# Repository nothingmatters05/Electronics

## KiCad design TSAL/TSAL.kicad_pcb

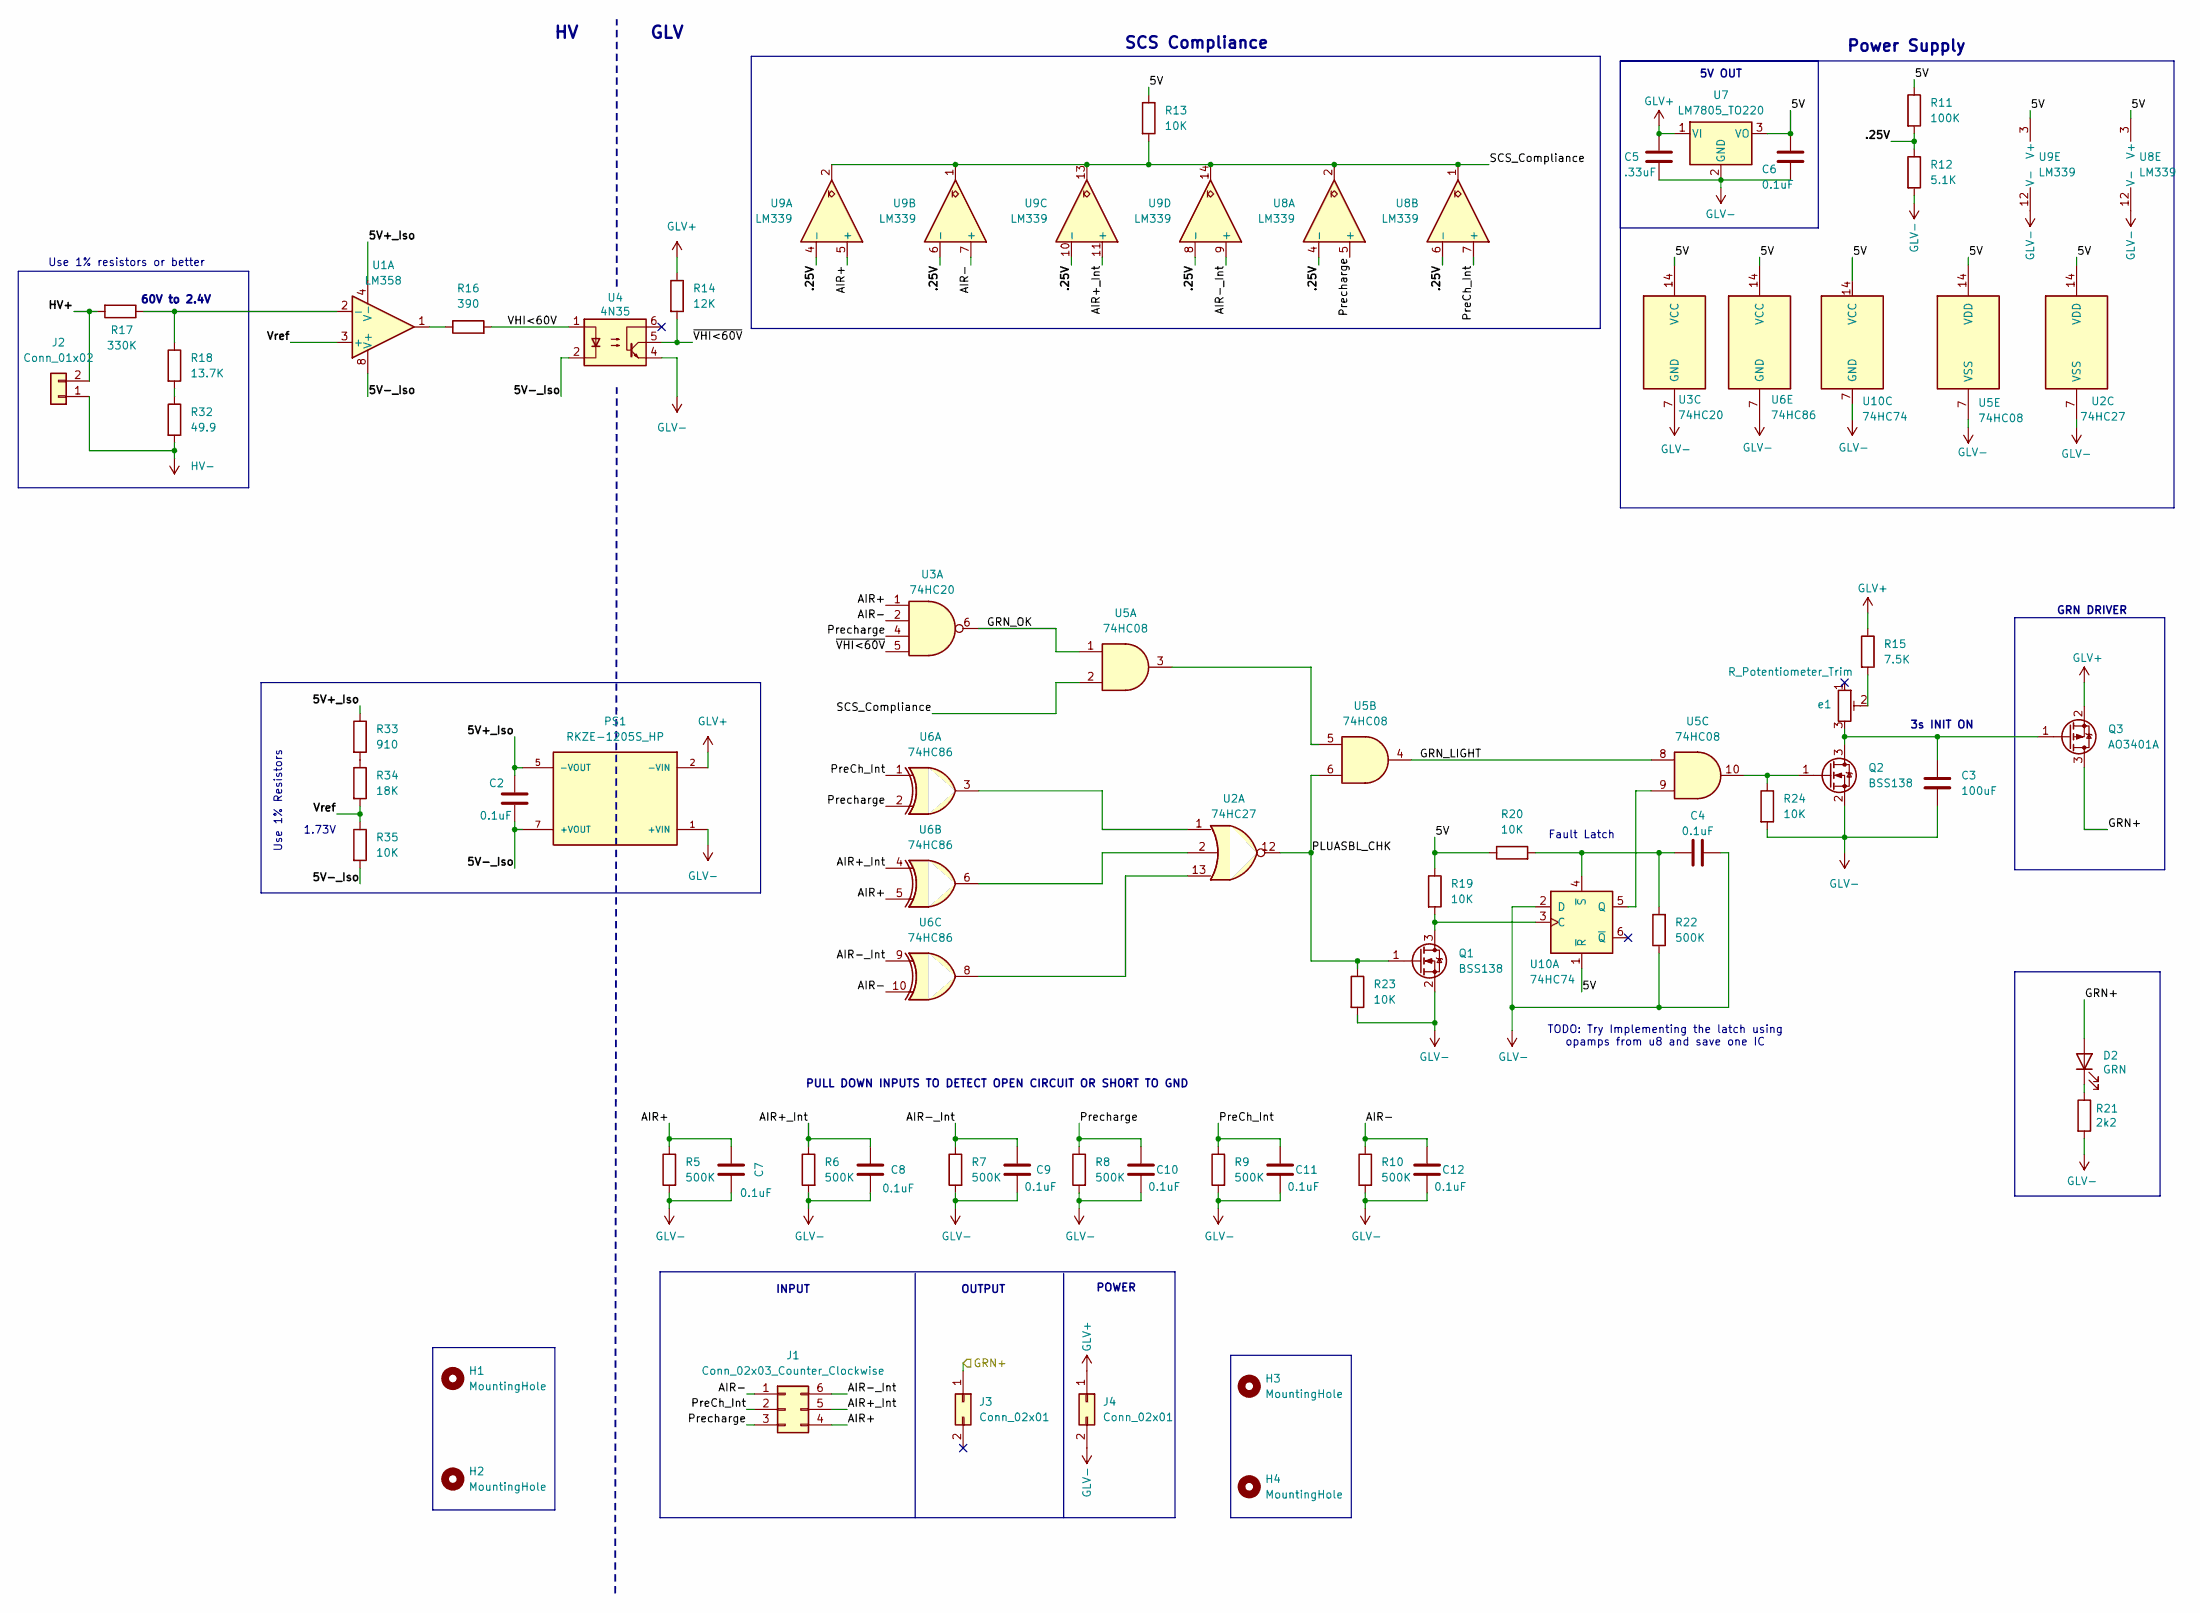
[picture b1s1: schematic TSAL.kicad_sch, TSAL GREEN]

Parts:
C2, C4, C6, C7, C8, C9, C10, C11, C12: 0.1uF; C_0603_1608Metric_Pad1.08x0.95mm_HandSolder
C3: 100uF; C_Elec_6.3x7.7
C5: .33uF; C_0603_1608Metric_Pad1.08x0.95mm_HandSolder
D2: GRN; LED_0805_2012Metric_Pad1.15x1.40mm_HandSolder
H1, H2, H3, H4: MountingHole; MountingHole_3.2mm_M3_DIN965
J1: Conn_02x03_Counter_Clockwise; Molex_Micro-Fit_3.0_43045-0612_2x03_P3.00mm_Vertical
J2: Conn_01x02; Molex_Mini-Fit_Jr_5566-02A_2x01_P4.20mm_Vertical
J3, J4: Conn_02x01; Molex_Micro-Fit_3.0_43045-0212_2x01_P3.00mm_Vertical
PS1: RKZE-1205S_HP; CONV_RKZE-1205S_HP
Q1, Q2: BSS138; SOT-23
Q3: AO3401A; SOT-23
R5, R6, R7, R8, R9, R10, R22: 500K; R_0603_1608Metric_Pad0.98x0.95mm_HandSolder
R11: 100K; R_0603_1608Metric_Pad0.98x0.95mm_HandSolder
R12: 5.1K; R_0603_1608Metric_Pad0.98x0.95mm_HandSolder
R13, R19, R20, R23, R24, R35: 10K; R_0603_1608Metric_Pad0.98x0.95mm_HandSolder
R14: 12K; R_0603_1608Metric_Pad0.98x0.95mm_HandSolder
R15: 7.5K; R_0603_1608Metric_Pad0.98x0.95mm_HandSolder
R16: 390; R_0603_1608Metric_Pad0.98x0.95mm_HandSolder
R17: 330K; R_1206_3216Metric_Pad1.30x1.75mm_HandSolder
R18: 13.7K; R_1206_3216Metric_Pad1.30x1.75mm_HandSolder
R21: 2k2; R_0603_1608Metric_Pad0.98x0.95mm_HandSolder
R32: 49.9; R_1206_3216Metric_Pad1.30x1.75mm_HandSolder
R33: 910; R_0603_1608Metric_Pad0.98x0.95mm_HandSolder
R34: 18K; R_0603_1608Metric_Pad0.98x0.95mm_HandSolder
U1: LM358; SOIC-8_3.9x4.9mm_P1.27mm
U2: 74HC27; SOIC-14_3.9x8.7mm_P1.27mm
U3: 74HC20; DIP-14_W7.62mm
U4: 4N35; DIP-6_W7.62mm
U5: 74HC08; DIP-14_W7.62mm
U6: 74HC86; DIP-14_W7.62mm
U7: LM7805_TO220; TO-220-3_Horizontal_TabDown
U8, U9: LM339; DIP-14_W7.62mm
U10: 74HC74; DIP-14_W7.62mm
e1: R_Potentiometer_Trim; Potentiometer_Bourns_3386F_Vertical

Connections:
/5V: C6.2, R11.1, R13.1, R19.1, R20.1, U2.14 (VDD), U3.14 (VCC), U5.14 (VDD), U6.14 (VCC), U7.3 (VO), U8.3 (V+), U9.3 (V+), U10.1 (~R), U10.14 (VCC)
/5V+_Iso: C2.1, PS1.5 (-VOUT), R33.1, U1.4 (V-)
/5V-_Iso: C2.2, PS1.7 (+VOUT), R35.2, U1.8 (V+), U4.2
/.25V: R11.2, R12.1, U8.4 (-), U8.6 (-), U9.4 (-), U9.6 (-), U9.8 (-), U9.10 (-)
/AIR+: C7.1, J1.4, R5.1, U3.1, U6.5, U9.5 (+)
/AIR+_Int: C8.1, J1.5, R6.1, U6.4, U9.11 (+)
/AIR-: C12.1, J1.1, R10.1, U3.2, U6.10, U9.7 (+)
/AIR-_Int: C9.1, J1.6, R7.1, U6.9, U9.9 (+)
/GRN+: D2.2 (A), J3.1, Q3.3 (D)
/GRN_LIGHT: U5.4, U5.8
/GRN_OK: U3.6, U5.1
/HV+: J2.2, R17.2
/PLUASBL_CHK: Q1.1 (G), U2.12, U5.6
/PreCh_Int: C11.1, J1.2, R9.1, U6.1, U8.7 (+)
/Precharge: C10.1, J1.3, R8.1, U3.4, U6.2, U8.5 (+)
/SCS_Compliance: R13.2, U5.2, U8.1, U8.2, U9.1, U9.2, U9.13, U9.14
/VHI<60V: R16.2, U4.1
/Vref: R34.2, R35.1, U1.3 (+)
/~VHI<60V: R14.2, U3.5, U4.5
GLV+: C5.1, J4.1, PS1.2 (-VIN), Q3.2 (S), R14.1, R15.1, U7.1 (VI)
GLV-: C3.2, C4.2, C5.2, C6.1, C7.2, C8.2, C9.2, C10.2, C11.2, C12.2, J4.2, PS1.1 (+VIN), Q1.2 (S), Q2.2 (S), R5.2, R6.2, R7.2, R8.2, R9.2, R10.2, R12.2, R21.2, R22.1, U2.7 (VSS), U3.7 (GND), U4.4, U5.7 (VSS), U6.7 (GND), U7.2 (GND), U8.12 (V-), U9.12 (V-), U10.2 (D), U10.7 (GND)
HV-: J2.1, R32.2
unnamed: D2.1 (K), R21.1
unnamed: Q1.3 (D), R19.2, U10.3 (C)
unnamed: C3.1, Q2.3 (D), Q3.1 (G), e1.3
unnamed: Q2.1 (G), U5.10
unnamed: R15.2, e1.2
unnamed: R16.1, U1.1
unnamed: R18.2, R32.1
unnamed: R33.2, R34.1
unnamed: R17.1, R18.1, U1.2 (-)
unnamed: U2.1, U6.3
unnamed: U2.2, U6.6
unnamed: U2.13, U6.8
unnamed: U5.3, U5.5
unnamed: U5.9, U10.5 (Q)
unnamed: C4.1, R20.2, R22.2, U10.4 (~S)

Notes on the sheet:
GLV
3s INIT ON
Power Supply
60V to 2.4V
GRN DRIVER
INPUT
TODO: Try Implementing the latch using opamps from u8 and save one IC
POWER
OUTPUT
PULL DOWN INPUTS TO DETECT OPEN CIRCUIT OR SHORT TO GND
Use 1% resistors or better
5V OUT
1.73V
SCS Compliance
Use 1% Resistors
Fault Latch

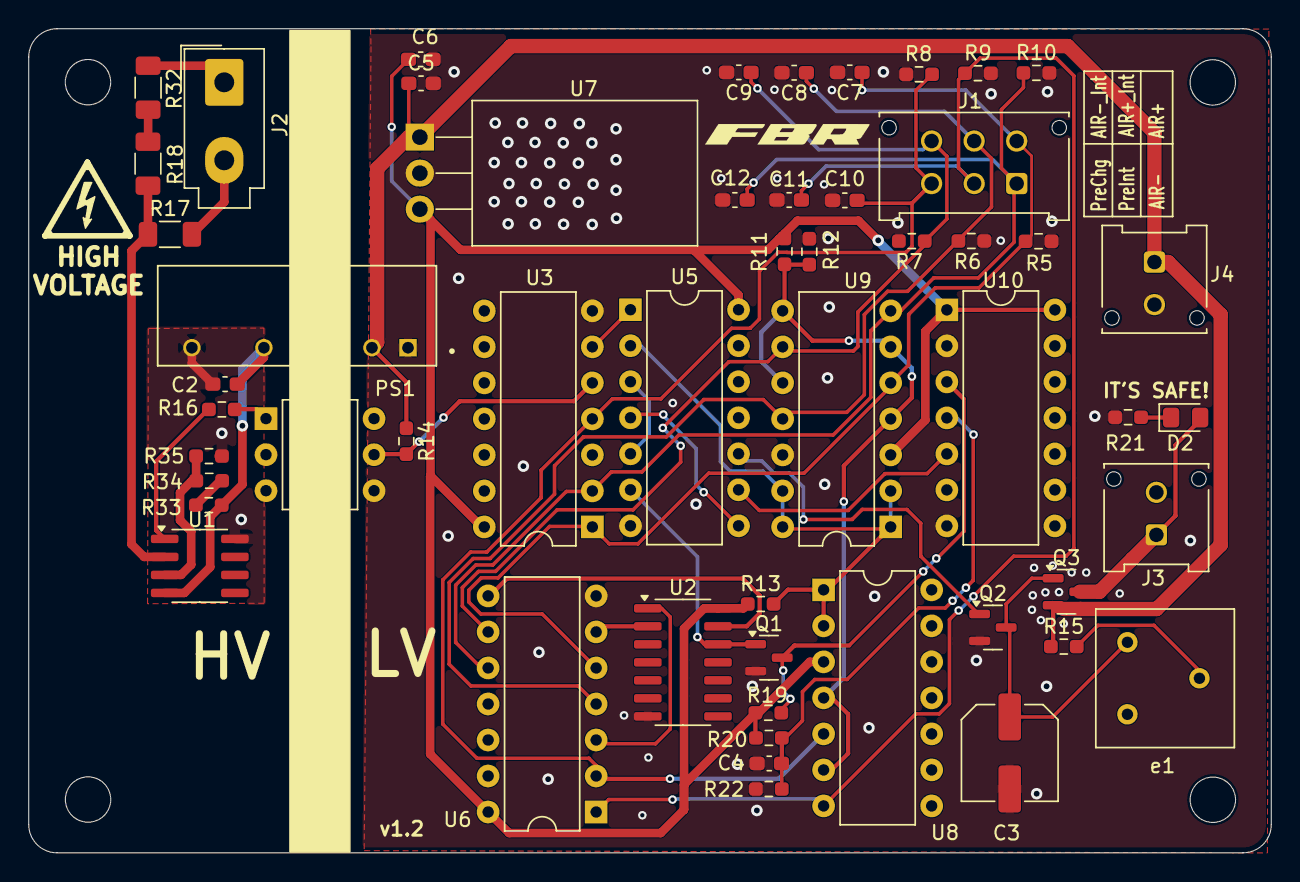
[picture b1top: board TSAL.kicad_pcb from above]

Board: 2 copper layers, 87.6 x 58.1 mm, 57 parts (0 on the bottom side), 37 nets.

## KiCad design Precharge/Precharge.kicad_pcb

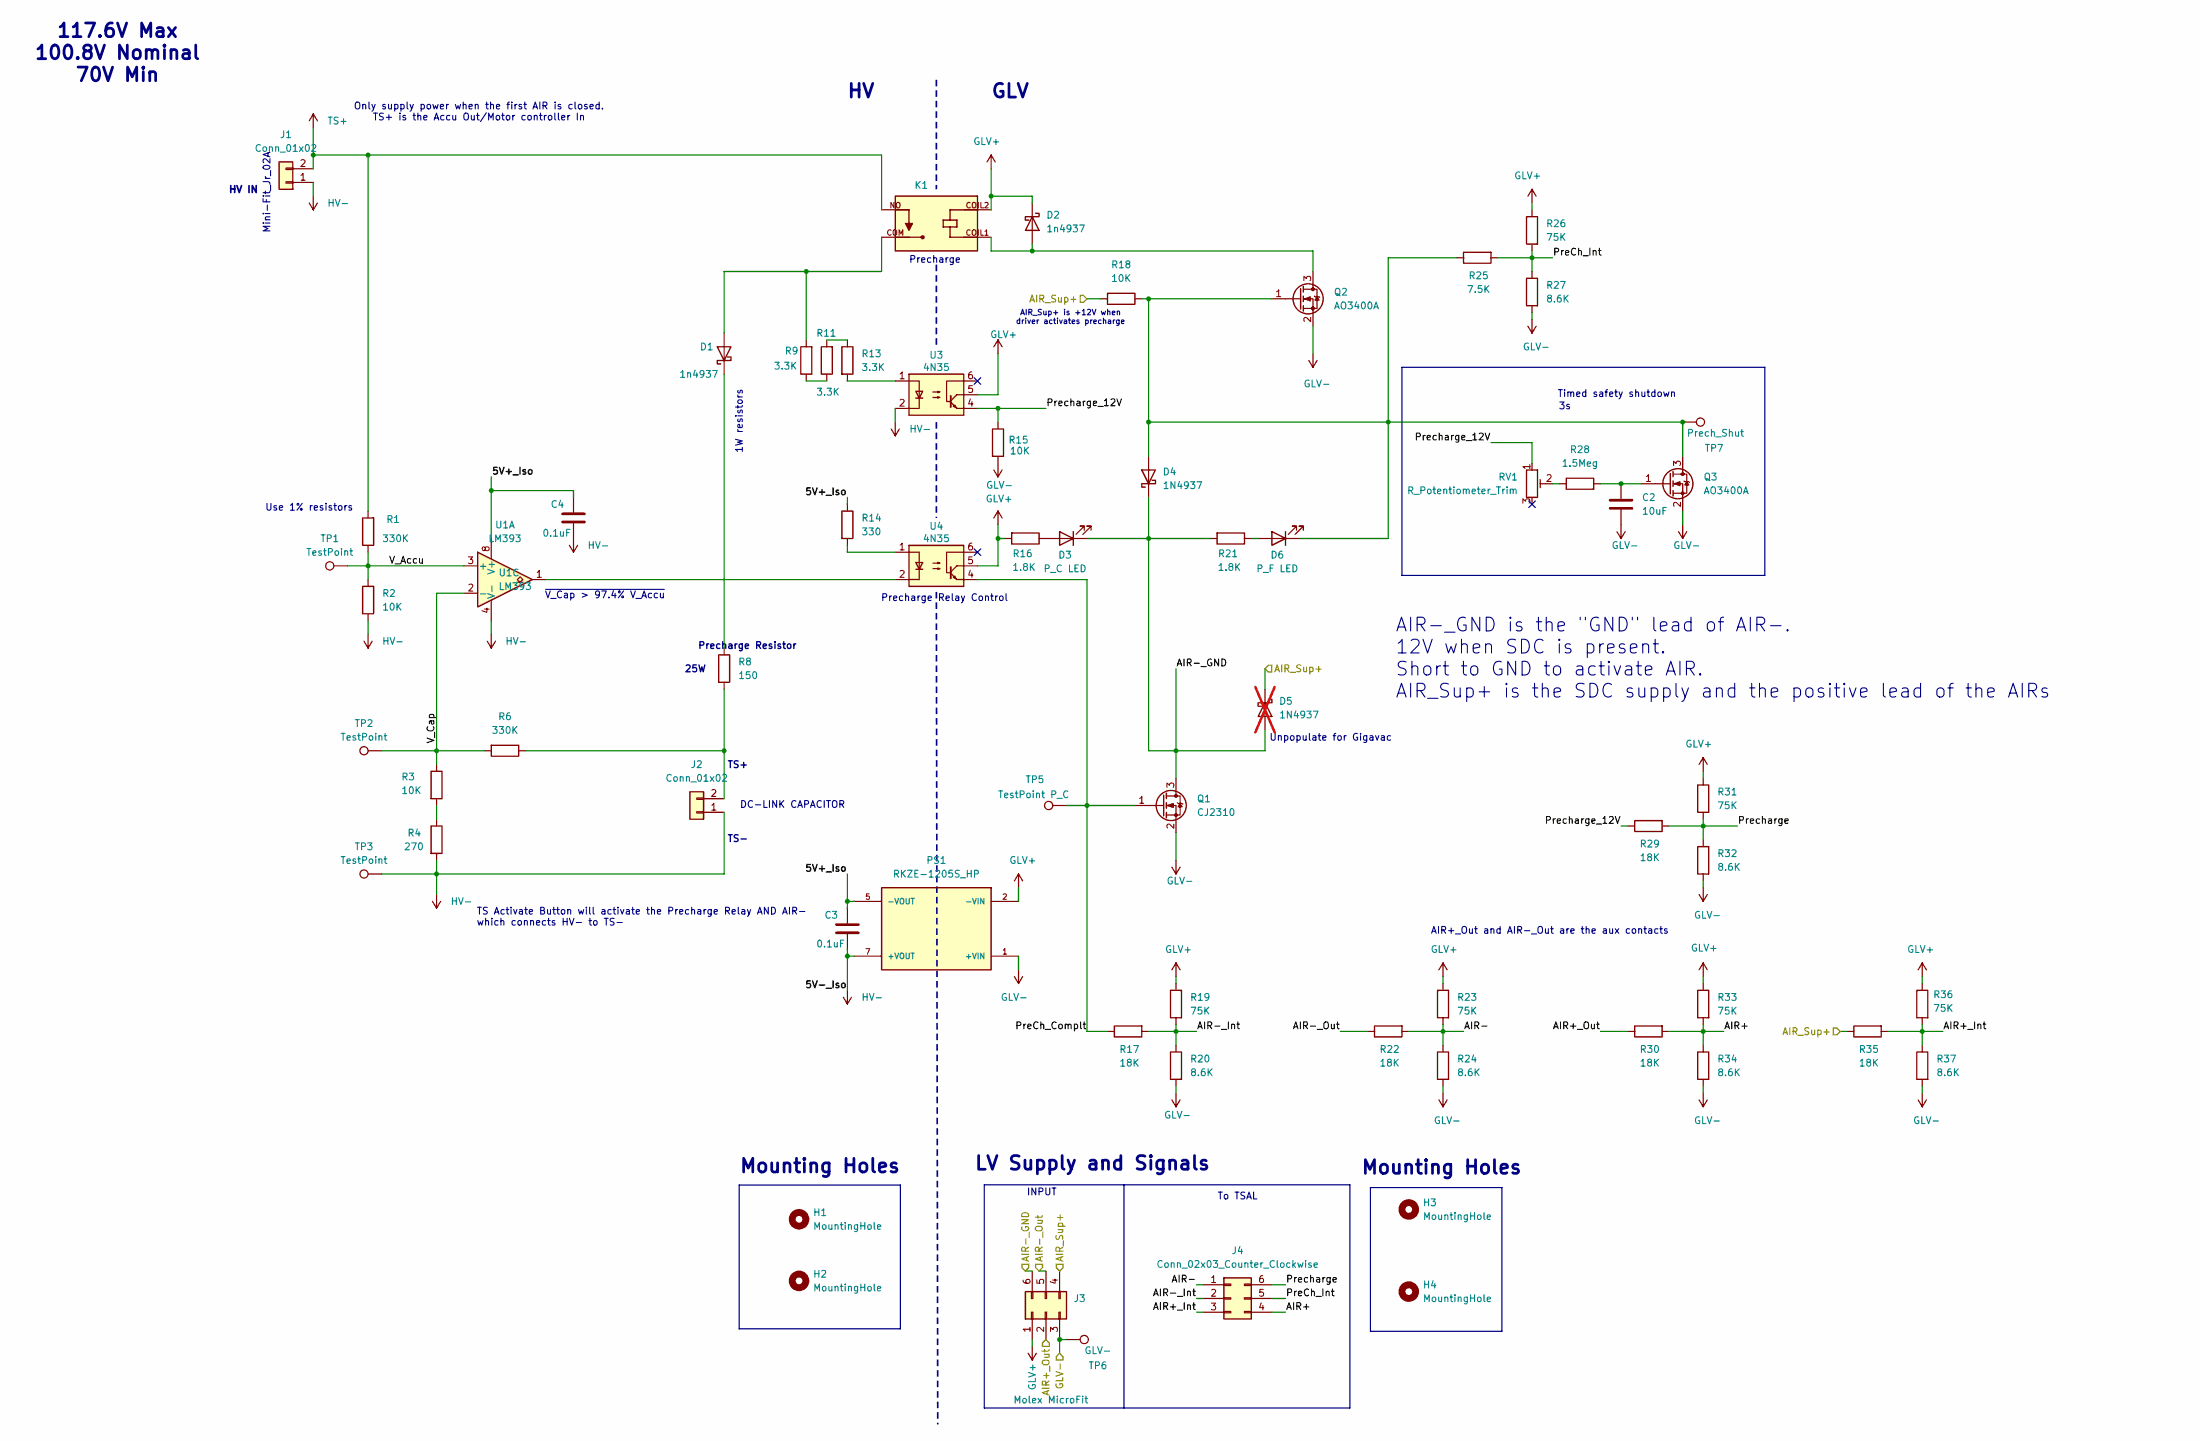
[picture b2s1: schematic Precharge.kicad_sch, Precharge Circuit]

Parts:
C2: 10uF; C_Elec_4x5.4
C3, C4: 0.1uF; C_0603_1608Metric_Pad1.08x0.95mm_HandSolder
D1, D2: 1n4937; D_DO-41_SOD81_P7.62mm_Horizontal
D3: P_C LED; LED_0805_2012Metric_Pad1.15x1.40mm_HandSolder
D4: 1N4937; D_DO-41_SOD81_P7.62mm_Horizontal
D5: 1N4937; D_DO-41_SOD81_P7.62mm_Horizontal; not fitted
D6: P_F LED; LED_0805_2012Metric_Pad1.15x1.40mm_HandSolder
H1, H2, H3, H4: MountingHole; MountingHole_3.2mm_M3_DIN965
J1, J2: Conn_01x02; Molex_Mini-Fit_Jr_5566-02A_2x01_P4.20mm_Vertical
J3: Molex MicroFit; Molex_Micro-Fit_3.0_43045-0612_2x03_P3.00mm_Vertical
J4: Conn_02x03_Counter_Clockwise; Molex_Micro-Fit_3.0_43045-0612_2x03_P3.00mm_Vertical
K1: KT12-1A-40L-THT; RELAY_KT12-1A-40L-THT; PARTREV 9
PS1: RKZE-1205S_HP; CONV_RKZE-1205S_HP
Q1: CJ2310; SOT-23
Q2, Q3: AO3400A; SOT-23
R1, R6: 330K; R_1206_3216Metric
R2, R3: 10K; R_1206_3216Metric
R4: 270; R_1206_3216Metric
R8: 150; HSA25
R9, R11, R13: 3.3K; R_2512_6332Metric_Pad1.40x3.35mm_HandSolder
R14: 330; R_0805_2012Metric_Pad1.20x1.40mm_HandSolder
R15, R18: 10K; R_0603_1608Metric_Pad0.98x0.95mm_HandSolder
R16, R21: 1.8K; R_0603_1608Metric_Pad0.98x0.95mm_HandSolder
R17, R22, R29, R30, R35: 18K; R_0603_1608Metric_Pad0.98x0.95mm_HandSolder
R19, R23, R26, R31, R33, R36: 75K; R_0603_1608Metric_Pad0.98x0.95mm_HandSolder
R20, R24, R27, R32, R34, R37: 8.6K; R_0603_1608Metric_Pad0.98x0.95mm_HandSolder
R25: 7.5K; R_0603_1608Metric_Pad0.98x0.95mm_HandSolder
R28: 1.5Meg; R_0805_2012Metric_Pad1.20x1.40mm_HandSolder
RV1: R_Potentiometer_Trim; Potentiometer_Bourns_3296W_Vertical
TP1, TP2, TP3: TestPoint; Pin_D1.0mm_L10.0mm
TP5: TestPoint P_C; Pin_D1.0mm_L10.0mm
TP6: GLV-; Pin_D1.0mm_L10.0mm
TP7: Prech_Shut; Pin_D1.0mm_L10.0mm
U1: LM393; SOIC-8_3.9x4.9mm_P1.27mm
U3, U4: 4N35; DIP-6_W7.62mm

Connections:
/5V+_Iso: C3.1, C4.1, PS1.5 (-VOUT), R14.1, U1.8 (V+)
/AIR+: J4.4, R30.2, R33.2, R34.1
/AIR+_Int: J4.3, R35.2, R36.2, R37.1
/AIR+_Out: J3.2, R30.1
/AIR-: J4.1, R22.2, R23.2, R24.1
/AIR-_GND: D3.1 (K), D4.1 (K), D5.2 (A), J3.6, Q1.3 (D), R21.2
/AIR-_Int: J4.2, R17.2, R19.2, R20.1
/AIR-_Out: J3.5, R22.1
/AIR_Sup+: D5.1 (K), J3.4, R18.2, R35.1
/PreCh_Complt: Q1.1 (G), R17.1, TP5.1 (1_1), U4.4
/PreCh_Int: J4.5, R25.2, R26.2, R27.1
/Precharge: J4.6, R29.2, R31.2, R32.1
/Precharge_12V: R15.1, R29.1, RV1.1, U3.4
/V_Accu: R1.1, R2.2, TP1.1 (1_1), U1.3 (+)
/V_Cap: R3.1, R6.2, TP2.1 (1_1), U1.2 (-)
GLV+: D2.1 (K), J3.1, K1.COIL2, PS1.2 (-VIN), R16.2, R19.1, R23.1, R26.1, R31.1, R33.1, R36.1, U3.5, U4.5
GLV-: C2.2, J3.3, PS1.1 (+VIN), Q1.2 (S), Q2.2 (S), Q3.2 (S), R15.2, R20.2, R24.2, R27.2, R32.2, R34.2, R37.2, TP6.1 (1_1)
HV-: C3.2, C4.2, J1.1, J2.1, PS1.7 (+VOUT), R2.1, R4.2, TP3.1 (1_1), U1.4 (V-), U3.2
unnamed: D1.2 (A), K1.COM, R9.2
unnamed: D1.1 (K), R8.1
unnamed: D2.2 (A), K1.COIL1, Q2.3 (D)
unnamed: D3.2 (A), R16.1
unnamed: D4.2 (A), D6.1 (K), Q2.1 (G), Q3.3 (D), R18.1, R25.1, TP7.1 (1_1)
unnamed: D6.2 (A), R21.1
unnamed: J2.2, R6.1, R8.2
unnamed: C2.1, Q3.1 (G), R28.2
unnamed: R3.2, R4.1
unnamed: R9.1, R11.1
unnamed: R11.2, R13.1
unnamed: R13.2, U3.1
unnamed: R14.2, U4.1
unnamed: R28.1, RV1.2
unnamed: U1.1, U4.2
TS+: J1.2, K1.NO, R1.2

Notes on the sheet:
Use 1% resistors
Precharge
TS+
HV IN
GLV
Mounting Holes
Precharge Resistor
LV Supply and Signals
DC-LINK CAPACITOR
Mini-Fit_Jr_02A
To TSAL
25W
~{V_Cap > 97.4% V_Accu}
Timed safety shutdown
Only supply power when the first AIR is closed. TS+ is the Accu Out/Motor controller In
TS Activate Button will activate the Precharge Relay AND AIR- which connects HV- to TS-
1W resistors
AIR+_Out and AIR-_Out are the aux contacts
AIR-_GND is the "GND" lead of AIR-. 12V when SDC is present. Short to GND to activate AIR. AIR_Sup+ is the SDC supply and the positive lead of the AIRs
117.6V Max 100.8V Nominal 70V Min
Precharge Relay Control
AIR_Sup+ is +12V when driver activates precharge
INPUT
Unpopulate for Gigavac
TS-

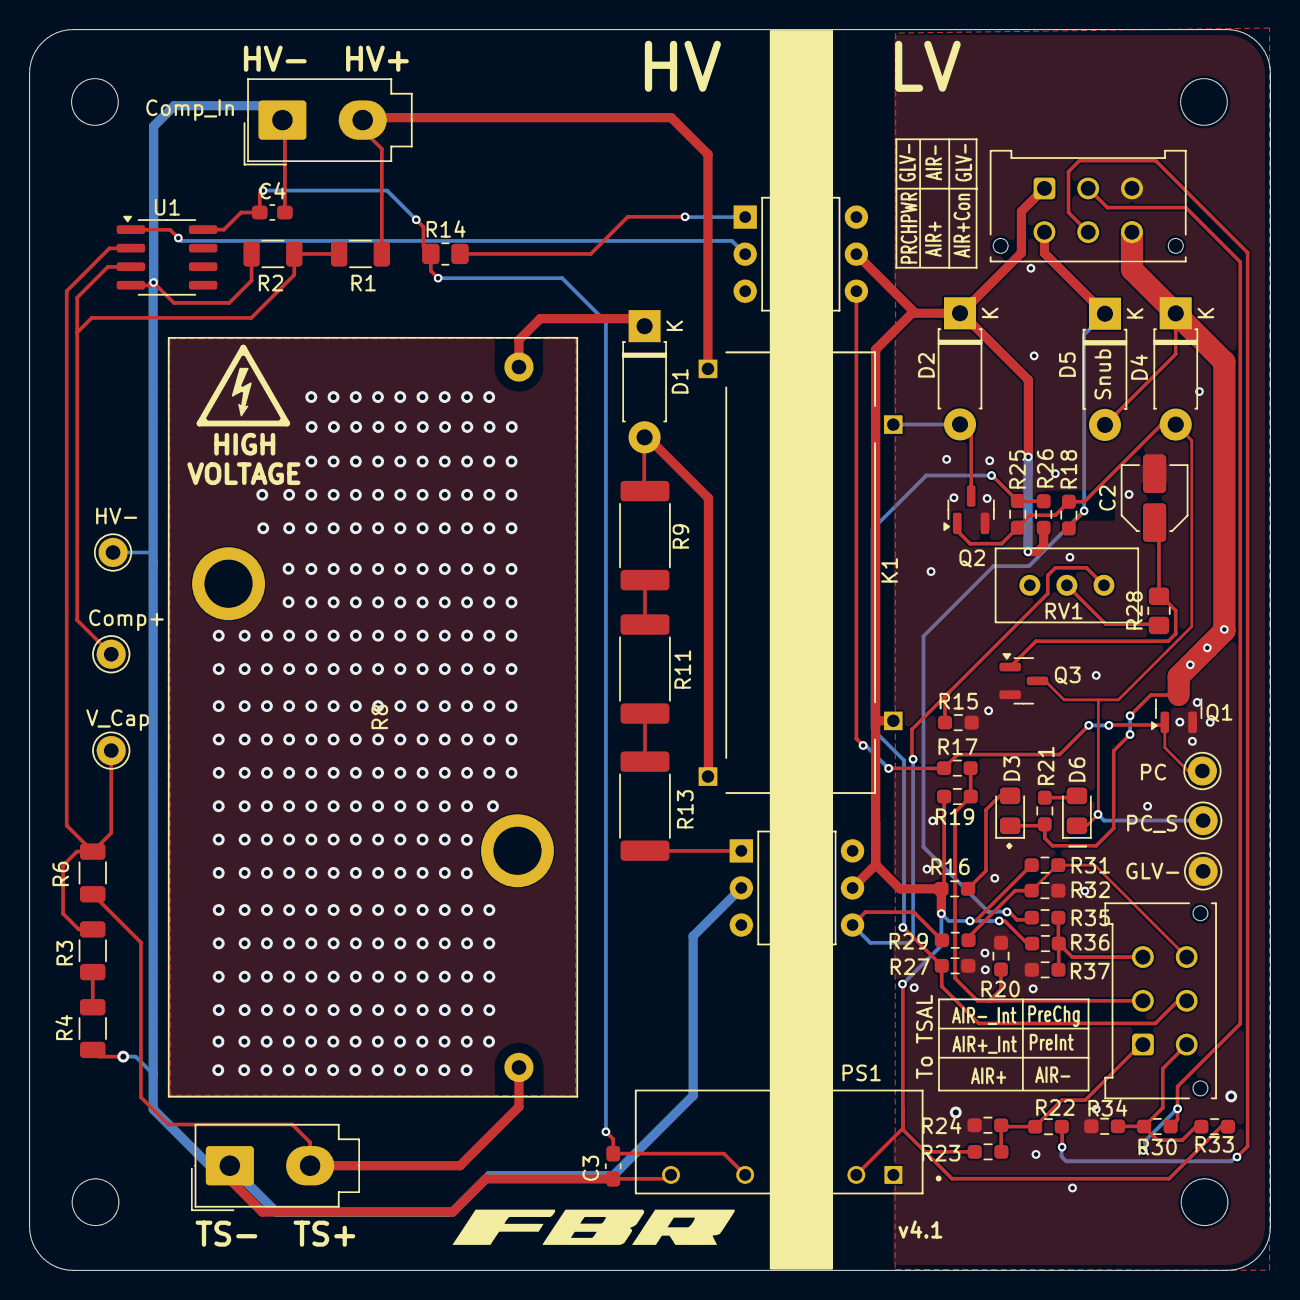
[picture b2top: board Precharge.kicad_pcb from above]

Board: 2 copper layers, 85.0 x 85.0 mm, 65 parts (0 on the bottom side), 34 nets.

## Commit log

2026-05-11 Precharge: Add isolated DC-DC
    New Precharge version
2026-06-19 Precharge: cap DC bias correction, PDs on TSAL
